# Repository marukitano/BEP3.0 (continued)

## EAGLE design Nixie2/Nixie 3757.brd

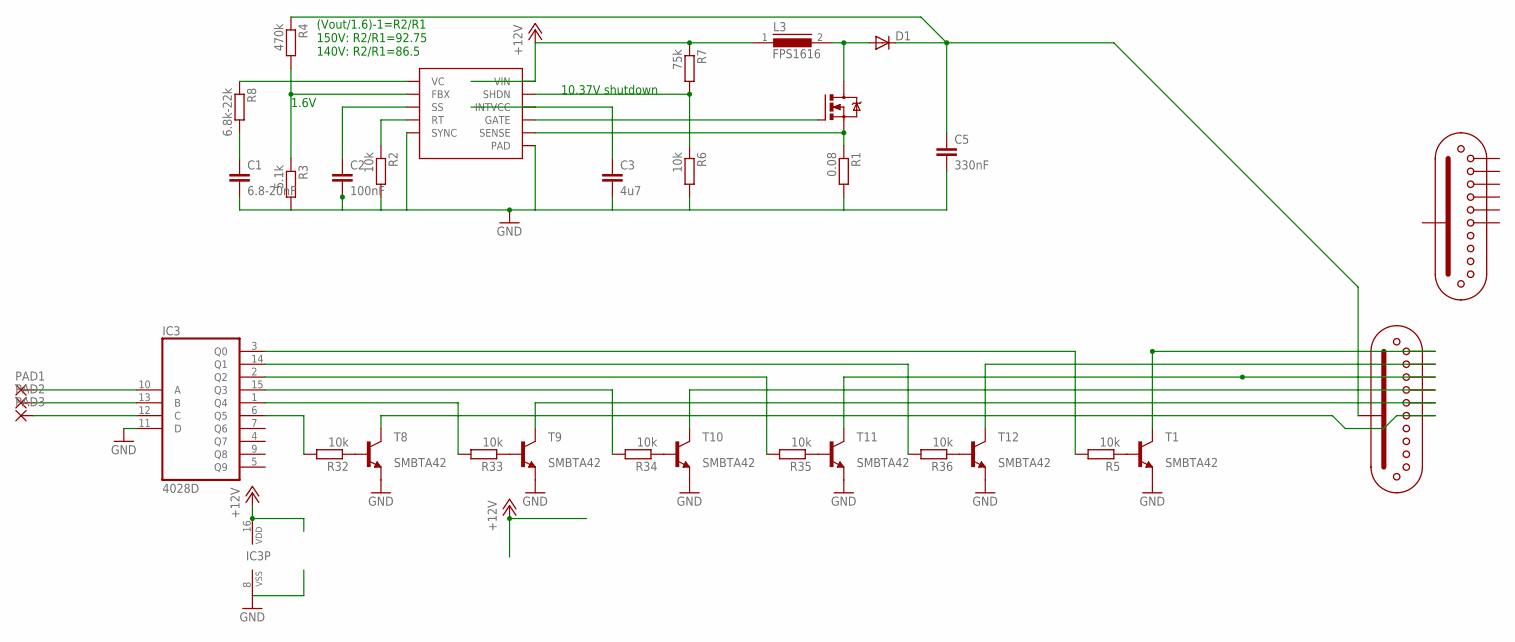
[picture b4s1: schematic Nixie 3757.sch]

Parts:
C1: 6.8-20nF; C0805K
C2: 100nF; C0805K
C3: 4u7; C0805K
C5: 330nF; C1812
D1: DIODE-DO219AB; DO219AB
IC3: 4028D; SO16
L3: FPS1616; 1616FPS_22UH
PAD1, PAD2, PAD3: 1,6/0,8
Q4: N-MOSFET-TO252-DPAK; TO252
R1: 0.08; R0805
R2, R5, R6, R32, R33, R34, R35, R36: 10k; R0805
R3: 5.1k; R0805
R4: 470k; R0805
R7: 75k; R0805
R8: 6.8k-22k; R0805
T1, T8, T9, T10, T11, T12: MMBTA42LT1-NPN-SOT23-BEC; SOT23-BEC
U1: LT3757MSOP-10; MSOP-10
U$1, U$3: ZM1020

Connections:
+12V: IC3.16 (VDD), L3.1, R7.1, U1.10 (VIN)
GND: C1.2, C2.2, C3.2, C5.2, IC3.8 (VSS), IC3.11 (D), R1.2, R2.2, R3.2, R6.2, T1.E, T8.E, T9.E, T10.E, T11.E, T12.E, U1.5 (SYNC), U1.PAD
unnamed: C2.1, U1.3 (SS)
unnamed: IC3.10 (A), PAD1.1
unnamed: IC3.13 (B), PAD2.1
unnamed: D1.A, L3.2, Q4.2 (D)
unnamed: R3.1, R4.2, U1.2 (FBX)
unnamed: IC3.3 (Q0), R5.2
unnamed: C1.1, R8.2
unnamed: C5.1, D1.C, R4.1, U$1.12 (A)
unnamed: Q4.1 (G), U1.7 (GATE)
unnamed: R2.1, U1.4 (RT)
unnamed: IC3.12 (C), PAD3.1
unnamed: R5.1, T1.B
unnamed: T1.C, U$1.11 (0)
unnamed: Q4.3 (S), R1.1, U1.6 (SENSE)
unnamed: R6.1, R7.2, U1.9 (SHDN)
unnamed: R8.1, U1.1 (VC)
unnamed: C3.1, U1.8 (INTVCC)
unnamed: R32.1, T8.B
unnamed: IC3.14 (Q1), R36.2
unnamed: IC3.2 (Q2), R35.2
unnamed: T10.C, U$1.3
unnamed: T9.C, U$1.4
unnamed: R34.1, T10.B
unnamed: R33.1, T9.B
unnamed: R35.1, T11.B
unnamed: IC3.6 (Q5), R32.2
unnamed: R36.1, T12.B
unnamed: T8.C, U$1.5
unnamed: IC3.1 (Q4), R33.2
unnamed: IC3.15 (Q3), R34.2
unnamed: T11.C, U$1.2
unnamed: T12.C, U$1.1

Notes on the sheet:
10.37V shutdown
1.6V
(Vout/1.6)-1=R2/R1 150V: R2/R1=92.75 140V: R2/R1=86.5

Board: 2 copper layers, 33 parts (1 on the bottom side), 34 nets, no tracks yet.

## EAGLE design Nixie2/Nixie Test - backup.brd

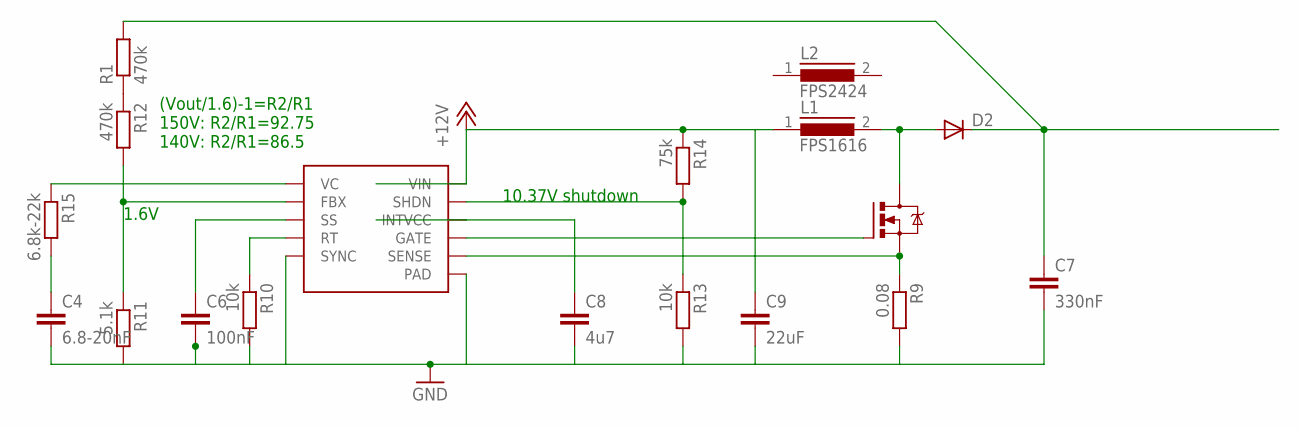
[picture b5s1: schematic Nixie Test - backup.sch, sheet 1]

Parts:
C4: 6.8-20nF; C0805K
C6: 100nF; C0805K
C7: 330nF; C1812
C8: 4u7; C1206K
C9: 22uF; C1210K
D2: DIODE-DO219AB; DO219AB
L1: FPS1616; 1616FPS_22UH
L2: FPS2424; 242408FPS_22UH
Q1: N-MOSFET-TO252-DPAK; TO252
R1, R12: 470k; R0805
R9: 0.08; R0805
R10, R13: 10k; R0805
R11: 5.1k; R0805
R14: 75k; R0805
R15: 6.8k-22k; R0805
U2: LT3757MSOP-10; MSOP-10

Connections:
+12V: C9.1, L1.1, R14.1, U2.10 (VIN); also elsewhere on the board
GND: C4.2, C6.2, C7.2, C8.2, C9.2, R9.2, R10.2, R11.2, R13.2, U2.5 (SYNC), U2.PAD; also elsewhere on the board
unnamed: R1.1, R12.1
unnamed: Q1.1 (G), U2.7 (GATE)
unnamed: R11.1, R12.2, U2.2 (FBX)
unnamed: D2.A, L1.2, Q1.3 (D)
unnamed: C7.1, D2.C, R1.2
unnamed: C6.1, U2.3 (SS)
unnamed: R10.1, U2.4 (RT)
unnamed: Q1.2 (S), R9.1, U2.6 (SENSE)
unnamed: R13.1, R14.2, U2.9 (SHDN)
unnamed: C4.1, R15.2
unnamed: R15.1, U2.1 (VC)
unnamed: C8.1, U2.8 (INTVCC)

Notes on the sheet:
10.37V shutdown
1.6V
(Vout/1.6)-1=R2/R1 150V: R2/R1=92.75 140V: R2/R1=86.5

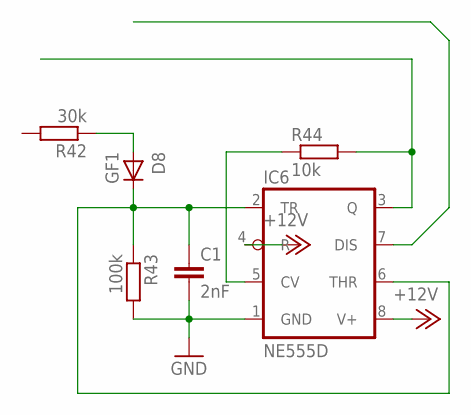
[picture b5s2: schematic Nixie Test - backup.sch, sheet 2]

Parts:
C1: 2nF; C1206K
D8: GF1; SMA-DO214AC
IC6: NE555D; SO08
R42: 30k; R0805
R43: 100k; R0805
R44: 10k; R0805

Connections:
+12V: IC6.4 (R), IC6.8 (V+); also elsewhere on the board
GND: C1.2, IC6.1 (GND), R43.2; also elsewhere on the board
unnamed: D8.A, R42.1
unnamed: IC6.3 (Q), R44.2
unnamed: IC6.5 (CV), R44.1
unnamed: C1.1, D8.K (C), IC6.2 (TR), IC6.6 (THR), R43.1

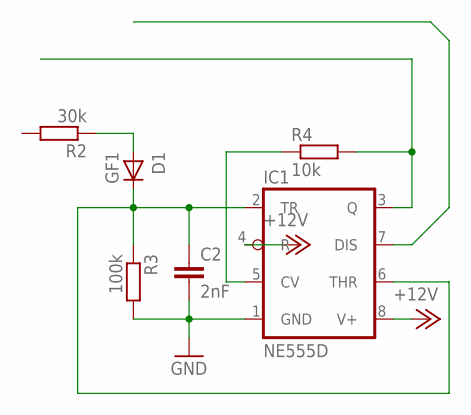
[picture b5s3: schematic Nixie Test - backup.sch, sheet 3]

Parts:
C2: 2nF; C1206K
D1: GF1; SMA-DO214AC
IC1: NE555D; SO08
R2: 30k; R0805
R3: 100k; R0805
R4: 10k; R0805

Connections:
+12V: IC1.4 (R), IC1.8 (V+); also elsewhere on the board
GND: C2.2, IC1.1 (GND), R3.2; also elsewhere on the board
unnamed: D1.A, R2.1
unnamed: IC1.5 (CV), R4.1
unnamed: C2.1, D1.K (C), IC1.2 (TR), IC1.6 (THR), R3.1
unnamed: IC1.3 (Q), R4.2

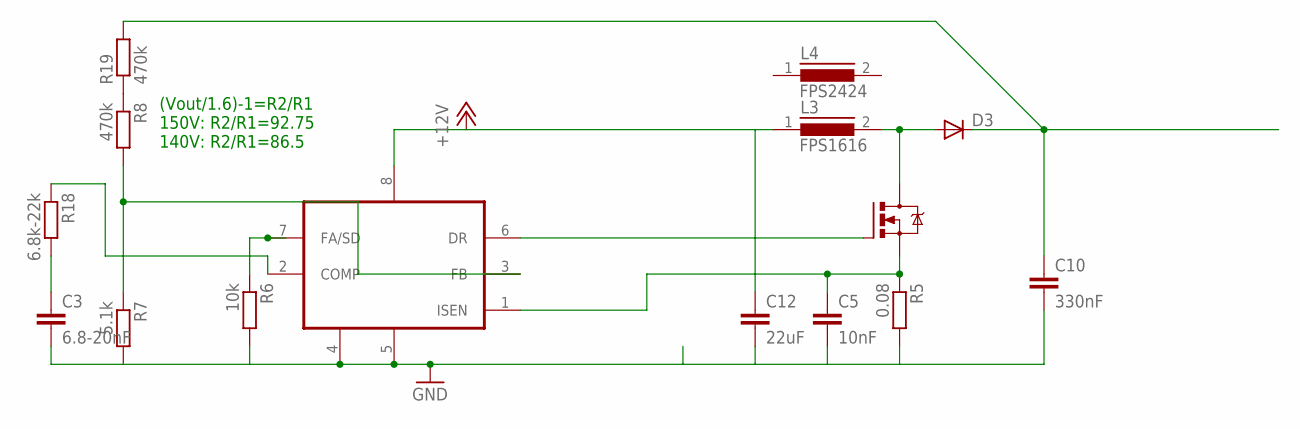
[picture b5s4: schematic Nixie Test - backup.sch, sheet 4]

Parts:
C3: 6.8-20nF; C0805K
C5: 10nF; C0805K
C10: 330nF; C1812
C12: 22uF; C1210K
D3: DIODE-DO219AB; DO219AB
L3: FPS1616; 1616FPS_22UH
L4: FPS2424; 242408FPS_22UH
Q2: N-MOSFET-TO252-DPAK; TO252
R5: 0.08; R0805
R6: 10k; R0805
R7: 5.1k; R0805
R8, R19: 470k; R0805
R18: 6.8k-22k; R0805
U3: LM3478; MSOP08

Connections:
+12V: C12.1, L3.1, U3.8 (VIN); also elsewhere on the board
GND: C3.2, C5.2, C10.2, C12.2, R5.2, R6.2, R7.2, U3.4 (AGND), U3.5 (PGND); also elsewhere on the board
unnamed: Q2.1 (G), U3.6 (DR)
unnamed: R7.1, R8.2, U3.3 (FB)
unnamed: D3.A, L3.2, Q2.3 (D)
unnamed: C10.1, D3.C, R19.2
unnamed: R18.1, U3.2 (COMP)
unnamed: R6.1, U3.7 (FA/SD)
unnamed: C5.1, Q2.2 (S), R5.1, U3.1 (ISEN)
unnamed: C3.1, R18.2
unnamed: R8.1, R19.1

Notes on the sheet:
(Vout/1.6)-1=R2/R1 150V: R2/R1=92.75 140V: R2/R1=86.5

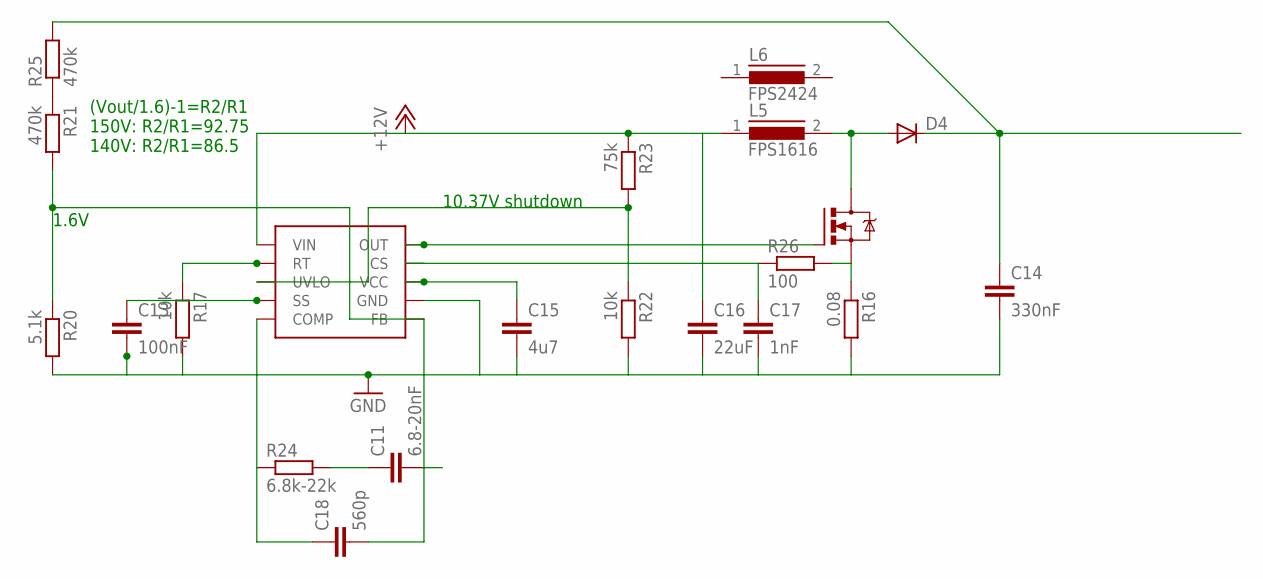
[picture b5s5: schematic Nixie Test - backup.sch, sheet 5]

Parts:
C11: 6.8-20nF; C0805K
C13: 100nF; C0805K
C14: 330nF; C1812
C15: 4u7; C1206K
C16: 22uF; C1210K
C17: 1nF; C0805K
C18: 560p; C0805K
D4: DIODE-DO219AB; DO219AB
L5: FPS1616; 1616FPS_22UH
L6: FPS2424; 242408FPS_22UH
Q3: N-MOSFET-TO252-DPAK; TO252
R16: 0.08; R0805
R17, R22: 10k; R0805
R20: 5.1k; R0805
R21, R25: 470k; R0805
R23: 75k; R0805
R24: 6.8k-22k; R0805
R26: 100; R0805
U4: LM5022MSOP-10; MSOP-10-NOPAD

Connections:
+12V: C16.1, L5.1, R23.1, U4.1 (VIN); also elsewhere on the board
GND: C13.2, C14.2, C15.2, C16.2, C17.2, R16.2, R17.2, R20.2, R22.2, U4.6 (GND); also elsewhere on the board
unnamed: Q3.1 (G), U4.5 (OUT)
unnamed: C11.2, C18.2, R20.1, R21.2, U4.2 (FB)
unnamed: D4.A, L5.2, Q3.3 (D)
unnamed: C14.1, D4.C, R25.2
unnamed: C13.1, U4.10 (SS)
unnamed: R17.1, U4.9 (RT)
unnamed: Q3.2 (S), R16.1, R26.2
unnamed: R22.1, R23.2, U4.7 (UVLO)
unnamed: C11.1, R24.2
unnamed: C18.1, R24.1, U4.3 (COMP)
unnamed: C15.1, U4.4 (VCC)
unnamed: R21.1, R25.1
unnamed: C17.1, R26.1, U4.8 (CS)

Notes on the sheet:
10.37V shutdown
1.6V
(Vout/1.6)-1=R2/R1 150V: R2/R1=92.75 140V: R2/R1=86.5

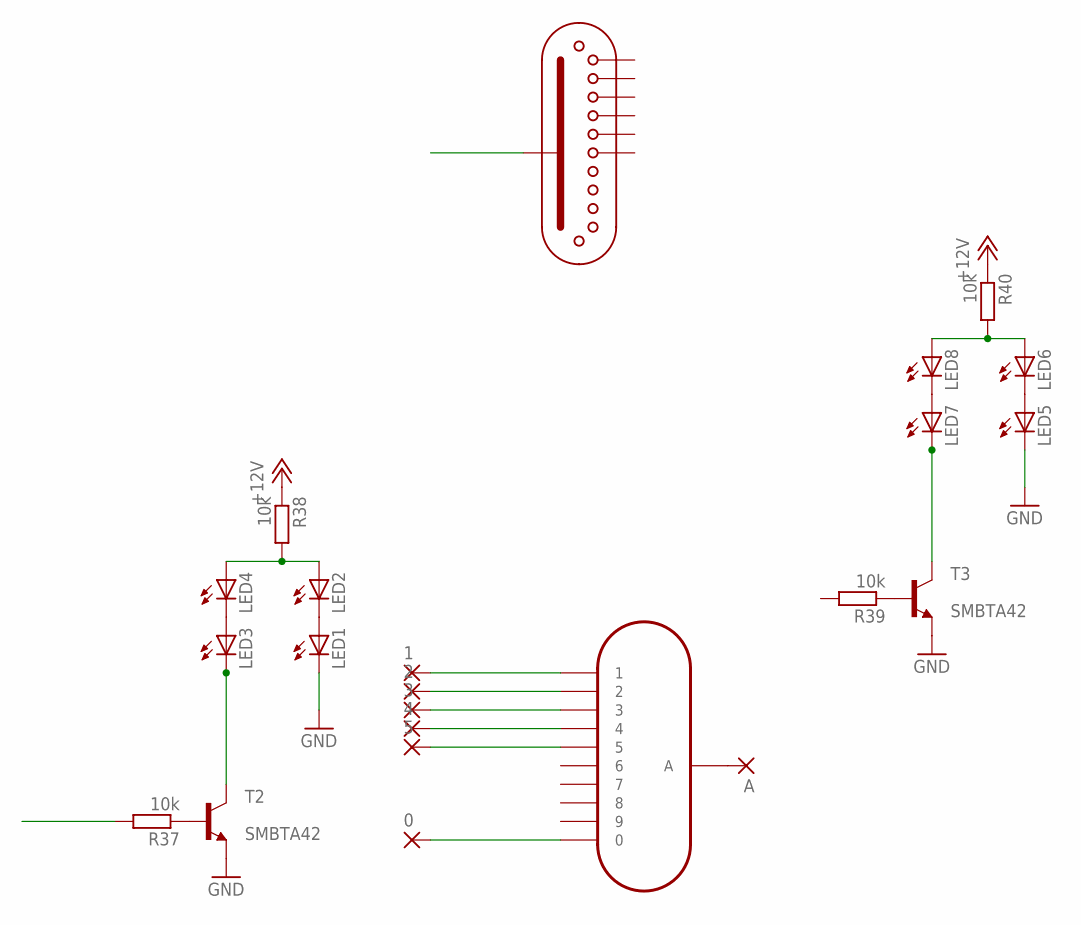
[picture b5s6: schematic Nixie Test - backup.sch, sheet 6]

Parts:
0, 1, 2, 3, 4, 5: SMD2; SMD1,27-2,54
A: SMD2; SMD1,27-2,54
LED1, LED2, LED3, LED4, LED5, LED6, LED7, LED8: LED3MM
N1: IN-12A-IN-12; IN-12
R37, R38, R39, R40: 10k; R0805
T2, T3: MMBTA42LT1-NPN-SOT23-BEC; SOT23-BEC
U$3: ZM1020

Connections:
+12V: R38.1, R40.1; also elsewhere on the board
GND: LED1.K (C), LED5.K (C), T2.E, T3.E; also elsewhere on the board
unnamed: LED1.A, LED2.K (C)
unnamed: LED3.A, LED4.K (C)
unnamed: R37.1, T2.B
unnamed: LED3.K (C), T2.C
unnamed: LED2.A, LED4.A, R38.2
unnamed: 0.1, N1.0
unnamed: 1.1, N1.1
unnamed: 2.1, N1.2
unnamed: 3.1, N1.3
unnamed: 4.1, N1.4
unnamed: 5.1, N1.5
unnamed: A.1, N1.A
unnamed: LED5.A, LED6.K (C)
unnamed: LED7.A, LED8.K (C)
unnamed: R39.1, T3.B
unnamed: LED7.K (C), T3.C
unnamed: LED6.A, LED8.A, R40.2

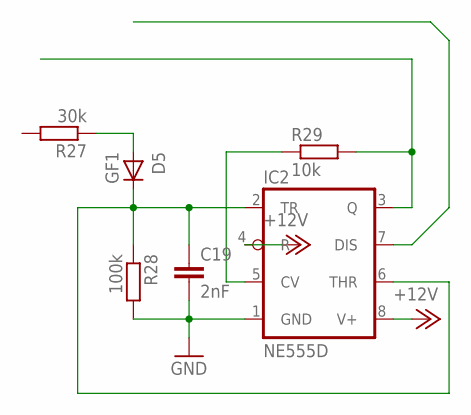
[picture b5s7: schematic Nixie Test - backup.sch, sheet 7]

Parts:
C19: 2nF; C1206K
D5: GF1; SMA-DO214AC
IC2: NE555D; SO08
R27: 30k; R0805
R28: 100k; R0805
R29: 10k; R0805

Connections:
+12V: IC2.4 (R), IC2.8 (V+); also elsewhere on the board
GND: C19.2, IC2.1 (GND), R28.2; also elsewhere on the board
unnamed: D5.A, R27.1
unnamed: IC2.5 (CV), R29.1
unnamed: C19.1, D5.K (C), IC2.2 (TR), IC2.6 (THR), R28.1
unnamed: IC2.3 (Q), R29.2

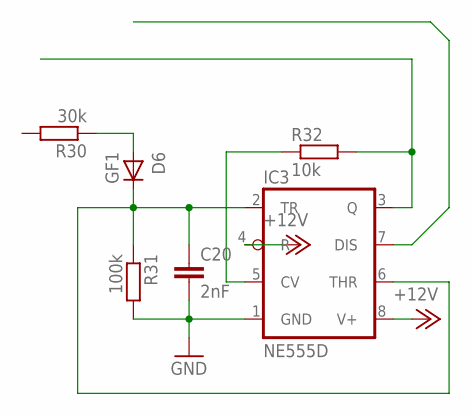
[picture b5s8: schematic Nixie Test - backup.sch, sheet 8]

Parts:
C20: 2nF; C1206K
D6: GF1; SMA-DO214AC
IC3: NE555D; SO08
R30: 30k; R0805
R31: 100k; R0805
R32: 10k; R0805

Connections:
+12V: IC3.4 (R), IC3.8 (V+); also elsewhere on the board
GND: C20.2, IC3.1 (GND), R31.2; also elsewhere on the board
unnamed: D6.A, R30.1
unnamed: IC3.5 (CV), R32.1
unnamed: C20.1, D6.K (C), IC3.2 (TR), IC3.6 (THR), R31.1
unnamed: IC3.3 (Q), R32.2

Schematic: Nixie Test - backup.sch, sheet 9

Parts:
C21: 2nF; C1206K
D7: GF1; SMA-DO214AC
IC4: NE555D; SO08
R33: 30k; R0805
R34: 100k; R0805
R35: 10k; R0805

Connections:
+12V: IC4.4 (R), IC4.8 (V+); also elsewhere on the board
GND: C21.2, IC4.1 (GND), R34.2; also elsewhere on the board
unnamed: D7.A, R33.1
unnamed: IC4.5 (CV), R35.1
unnamed: C21.1, D7.K (C), IC4.2 (TR), IC4.6 (THR), R34.1
unnamed: IC4.3 (Q), R35.2

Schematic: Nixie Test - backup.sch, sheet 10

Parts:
C22: 2nF; C1206K
D9: GF1; SMA-DO214AC
IC5: NE555D; SO08
R36: 30k; R0805
R41: 100k; R0805
R45: 10k; R0805

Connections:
+12V: IC5.4 (R), IC5.8 (V+); also elsewhere on the board
GND: C22.2, IC5.1 (GND), R41.2; also elsewhere on the board
unnamed: D9.A, R36.1
unnamed: IC5.5 (CV), R45.1
unnamed: C22.1, D9.K (C), IC5.2 (TR), IC5.6 (THR), R41.1
unnamed: IC5.3 (Q), R45.2

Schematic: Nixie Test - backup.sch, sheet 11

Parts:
C23: 6.8-20nF; C0805K
C24: 100nF; C0805K
C25: 330nF; C1812
C26: 4u7; C1206K
C27: 22uF; C1210K
D10: DIODE-DO219AB; DO219AB
L7: FPS1616; 1616FPS_22UH
L8: FPS2424; 242408FPS_22UH
Q4: N-MOSFET-TO252-DPAK; TO252
R46: 0.08; R0805
R47, R50: 10k; R0805
R48: 5.1k; R0805
R49, R53: 470k; R0805
R51: 75k; R0805
R52: 6.8k-22k; R0805
U1: LT3757MSOP-10; MSOP-10

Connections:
+12V: C27.1, L7.1, R51.1, U1.10 (VIN); also elsewhere on the board
GND: C23.2, C24.2, C25.2, C26.2, C27.2, R46.2, R47.2, R48.2, R50.2, U1.5 (SYNC), U1.PAD; also elsewhere on the board
unnamed: Q4.1 (G), U1.7 (GATE)
unnamed: R48.1, R49.2, U1.2 (FBX)
unnamed: D10.A, L7.2, Q4.3 (D)
unnamed: C25.1, D10.C, R53.2
unnamed: C24.1, U1.3 (SS)
unnamed: R47.1, U1.4 (RT)
unnamed: Q4.2 (S), R46.1, U1.6 (SENSE)
unnamed: R50.1, R51.2, U1.9 (SHDN)
unnamed: C23.1, R52.2
unnamed: R52.1, U1.1 (VC)
unnamed: C26.1, U1.8 (INTVCC)
unnamed: R49.1, R53.1

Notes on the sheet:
10.37V shutdown
1.6V
(Vout/1.6)-1=R2/R1 150V: R2/R1=92.75 140V: R2/R1=86.5

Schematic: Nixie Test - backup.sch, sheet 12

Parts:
C28: 2nF; C1206K
D11: GF1; SMA-DO214AC
IC7: NE555D; SO08
R54: 30k; R0805
R55: 100k; R0805
R56: 10k; R0805

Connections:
+12V: IC7.4 (R), IC7.8 (V+); also elsewhere on the board
GND: C28.2, IC7.1 (GND), R55.2; also elsewhere on the board
unnamed: D11.A, R54.1
unnamed: IC7.5 (CV), R56.1
unnamed: C28.1, D11.K (C), IC7.2 (TR), IC7.6 (THR), R55.1
unnamed: IC7.3 (Q), R56.2

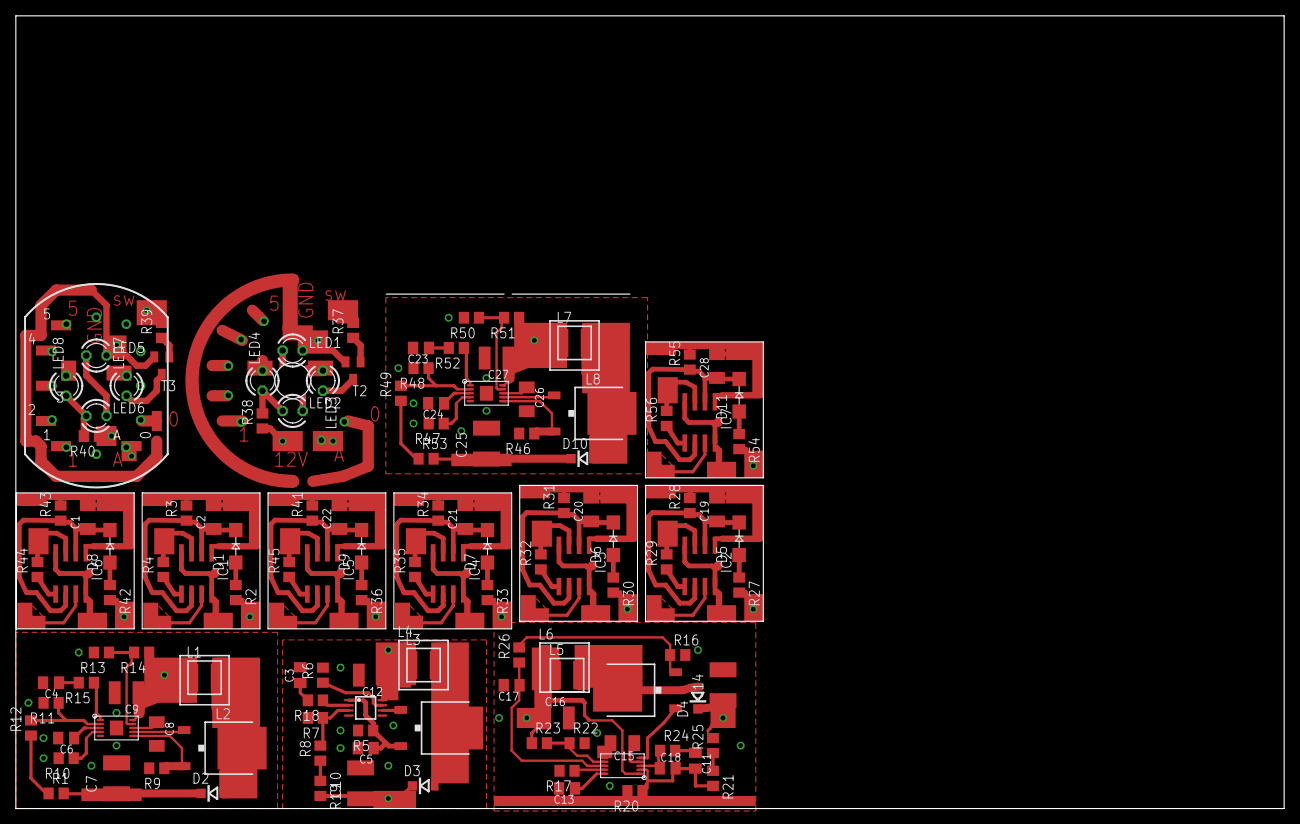
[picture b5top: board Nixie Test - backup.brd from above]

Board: 2 copper layers, 160.0 x 100.0 mm, 137 parts (0 on the bottom side), 93 nets.
